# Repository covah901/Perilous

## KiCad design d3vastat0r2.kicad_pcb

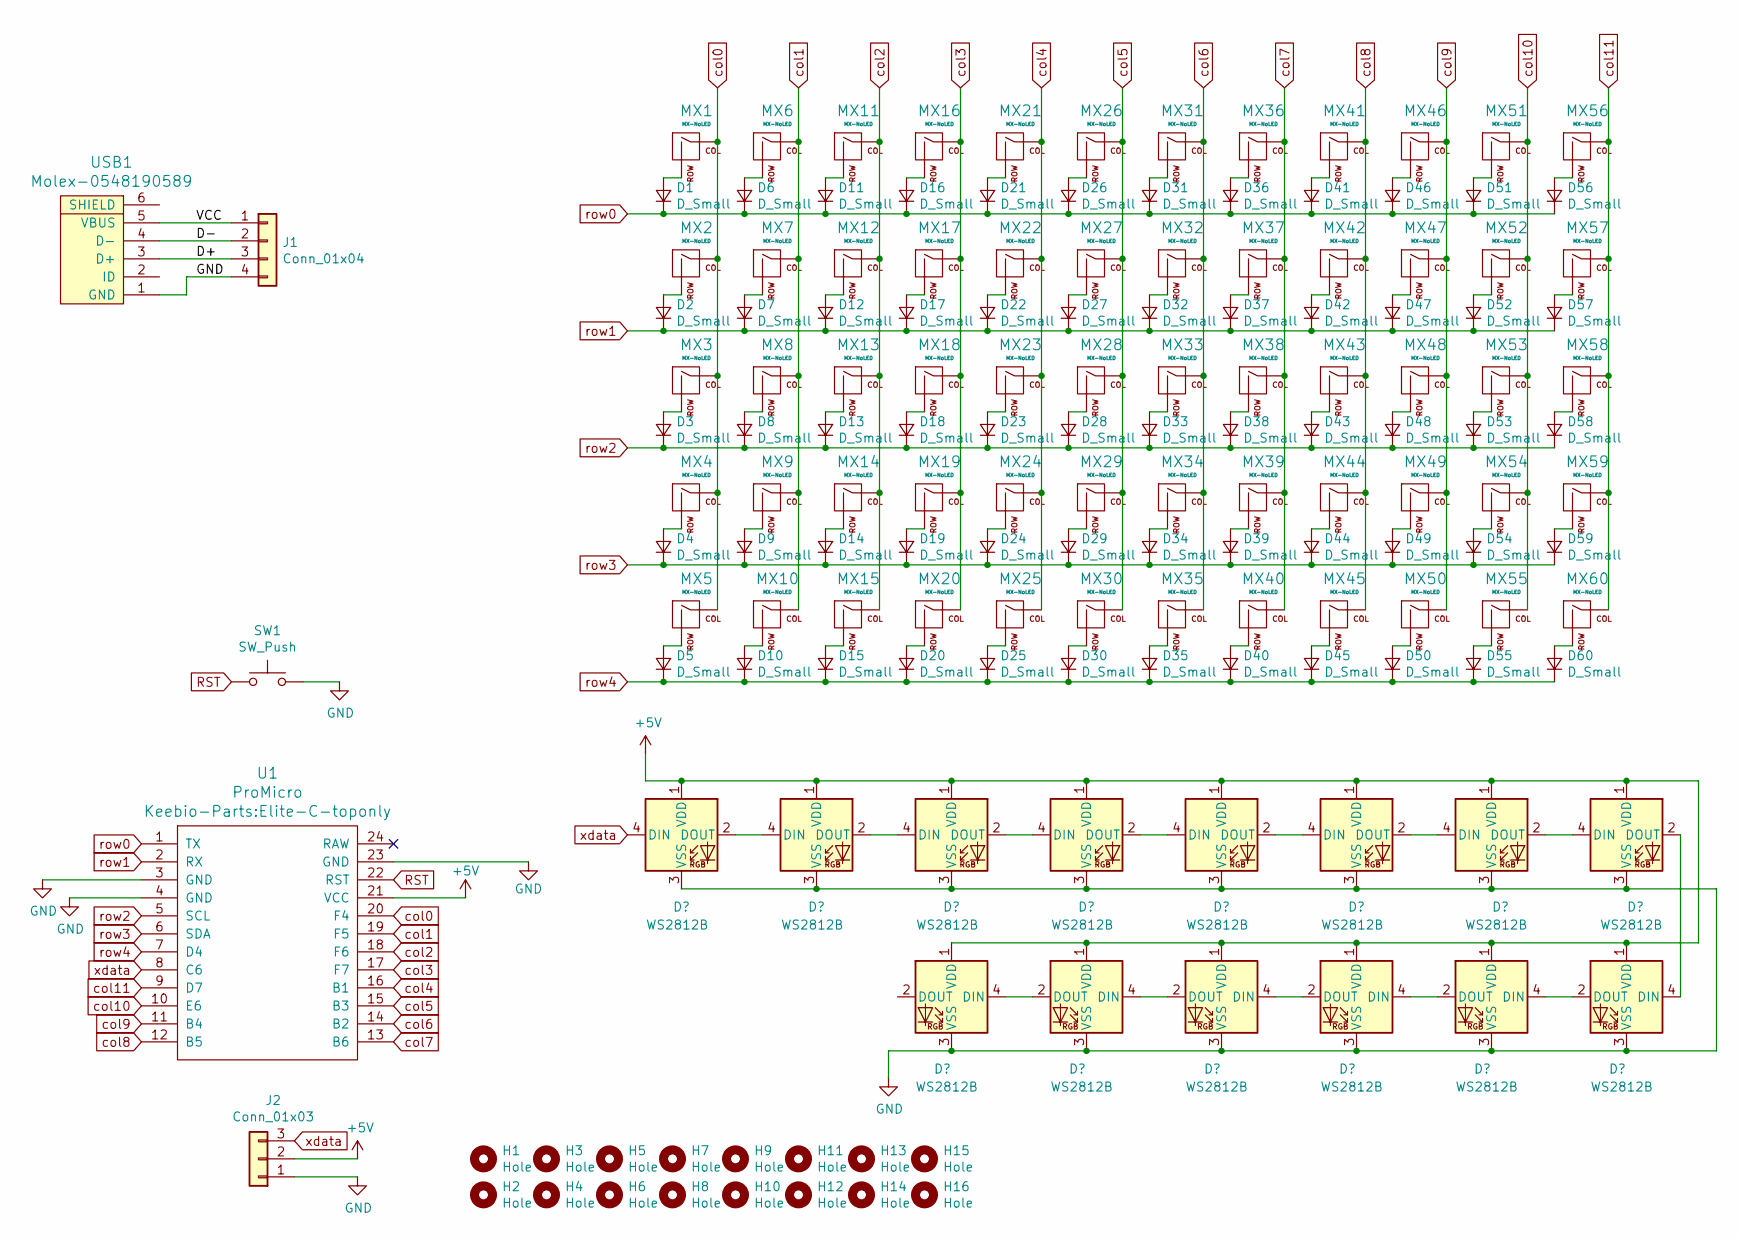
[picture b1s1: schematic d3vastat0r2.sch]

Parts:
D1, D2, D3, D4, D5, D6, D7, D8, D9, D10, D11, D12, D13, D14, D15, D16, D17, D18, D19, D20, D21, D22, D23, D24, D25, D26, D27, D28, D29, D30, D31, D32, D33, D34, D35, D36, D37, D38, D39, D40, D41, D42, D43, D44, D45, D46, D47, D48, D49, D50, D51, D52, D53, D54, D55, D56, D57, D58, D59, D60: D_Small; Diode-dual
H1, H2, H3, H4, H5, H6, H7, H8, H9, H10, H11, H12, H13, H14, H15, H16: Hole; MountingHole_2.2mm_M2_DIN965_Pad
J1: Conn_01x04; SolderWirePad_1x04_P3.81mm_Drill1mm
J2: Conn_01x03; SolderWirePad_1x03_P3.175mm_Drill1mm
MX1, MX5, MX6, MX7, MX8, MX9, MX10, MX11, MX12, MX13, MX14, MX15, MX16, MX17, MX18, MX19, MX21, MX22, MX23, MX24, MX26, MX27, MX28, MX29, MX31, MX32, MX33, MX34, MX36, MX37, MX38, MX39, MX41, MX42, MX43, MX44, MX45, MX46, MX47, MX48, MX49, MX50, MX51, MX52, MX53, MX54, MX55, MX56, MX60: MX-NoLED; MXOnly-1U-NoLED
MX2, MX20, MX25, MX40, MX57: MX-NoLED; MXOnly-1.5U-NoLED
MX3: MX-NoLED; MXOnly-1.75U-NoLED
MX4, MX58, MX59: MX-NoLED; MXOnly-2.25U-NoLED
MX30, MX35: MX-NoLED; MXOnly-2U-NoLED
SW1: SW_Push; SKQG-1155865
U1: ProMicro; Elite-C-toponly
USB1: Molex-0548190589; USB-Mini-B_ LCSC-C46398

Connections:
+5V: J2.2, U1.21 (VCC)
/D+: J1.3, USB1.3 (D+)
/D-: J1.2, USB1.4 (D-)
/VCC: J1.1, USB1.5 (VBUS)
GND: J1.4, J2.1, SW1.2, U1.3 (GND), U1.4 (GND), U1.23 (GND), USB1.1 (GND)
unnamed: D1.2 (A), MX1.2 (ROW)
unnamed: D2.2 (A), MX2.2 (ROW)
unnamed: D3.2 (A), MX3.2 (ROW)
unnamed: D4.2 (A), MX4.2 (ROW)
unnamed: D5.2 (A), MX5.2 (ROW)
unnamed: D6.2 (A), MX6.2 (ROW)
unnamed: D7.2 (A), MX7.2 (ROW)
unnamed: D8.2 (A), MX8.2 (ROW)
unnamed: D9.2 (A), MX9.2 (ROW)
unnamed: D10.2 (A), MX10.2 (ROW)
unnamed: D11.2 (A), MX11.2 (ROW)
unnamed: D12.2 (A), MX12.2 (ROW)
unnamed: D13.2 (A), MX13.2 (ROW)
unnamed: D14.2 (A), MX14.2 (ROW)
unnamed: D15.2 (A), MX15.2 (ROW)
unnamed: D16.2 (A), MX16.2 (ROW)
unnamed: D17.2 (A), MX17.2 (ROW)
unnamed: D18.2 (A), MX18.2 (ROW)
unnamed: D19.2 (A), MX19.2 (ROW)
unnamed: D20.2 (A), MX20.2 (ROW)
unnamed: D21.2 (A), MX21.2 (ROW)
unnamed: D22.2 (A), MX22.2 (ROW)
unnamed: D23.2 (A), MX23.2 (ROW)
unnamed: D24.2 (A), MX24.2 (ROW)
unnamed: D25.2 (A), MX25.2 (ROW)
unnamed: D26.2 (A), MX26.2 (ROW)
unnamed: D27.2 (A), MX27.2 (ROW)
unnamed: D28.2 (A), MX28.2 (ROW)
unnamed: D29.2 (A), MX29.2 (ROW)
unnamed: D30.2 (A), MX30.2 (ROW)
unnamed: D31.2 (A), MX31.2 (ROW)
unnamed: D32.2 (A), MX32.2 (ROW)
unnamed: D33.2 (A), MX33.2 (ROW)
unnamed: D34.2 (A), MX34.2 (ROW)
unnamed: D35.2 (A), MX35.2 (ROW)
unnamed: D36.2 (A), MX36.2 (ROW)
unnamed: D37.2 (A), MX37.2 (ROW)
unnamed: D38.2 (A), MX38.2 (ROW)
unnamed: D39.2 (A), MX39.2 (ROW)
unnamed: D40.2 (A), MX40.2 (ROW)
unnamed: D41.2 (A), MX41.2 (ROW)
unnamed: D42.2 (A), MX42.2 (ROW)
unnamed: D43.2 (A), MX43.2 (ROW)
unnamed: D44.2 (A), MX44.2 (ROW)
unnamed: D45.2 (A), MX45.2 (ROW)
unnamed: D46.2 (A), MX46.2 (ROW)
unnamed: D47.2 (A), MX47.2 (ROW)
unnamed: D48.2 (A), MX48.2 (ROW)
unnamed: D49.2 (A), MX49.2 (ROW)
unnamed: D50.2 (A), MX50.2 (ROW)
unnamed: D51.2 (A), MX51.2 (ROW)
unnamed: D52.2 (A), MX52.2 (ROW)
unnamed: D53.2 (A), MX53.2 (ROW)
unnamed: D54.2 (A), MX54.2 (ROW)
unnamed: D55.2 (A), MX55.2 (ROW)
unnamed: D56.2 (A), MX56.2 (ROW)
unnamed: D57.2 (A), MX57.2 (ROW)
unnamed: D58.2 (A), MX58.2 (ROW)
unnamed: D59.2 (A), MX59.2 (ROW)
unnamed: D60.2 (A), MX60.2 (ROW)
RST: SW1.1, U1.22 (RST)
col0: MX1.1 (COL), MX2.1 (COL), MX3.1 (COL), MX4.1 (COL), MX5.1 (COL), U1.20 (F4)
col1: MX6.1 (COL), MX7.1 (COL), MX8.1 (COL), MX9.1 (COL), MX10.1 (COL), U1.19 (F5)
col2: MX11.1 (COL), MX12.1 (COL), MX13.1 (COL), MX14.1 (COL), MX15.1 (COL), U1.18 (F6)
col3: MX16.1 (COL), MX17.1 (COL), MX18.1 (COL), MX19.1 (COL), MX20.1 (COL), U1.17 (F7)
col4: MX21.1 (COL), MX22.1 (COL), MX23.1 (COL), MX24.1 (COL), MX25.1 (COL), U1.16 (B1)
col5: MX26.1 (COL), MX27.1 (COL), MX28.1 (COL), MX29.1 (COL), MX30.1 (COL), U1.15 (B3)
col6: MX31.1 (COL), MX32.1 (COL), MX33.1 (COL), MX34.1 (COL), MX35.1 (COL), U1.14 (B2)
col7: MX36.1 (COL), MX37.1 (COL), MX38.1 (COL), MX39.1 (COL), MX40.1 (COL), U1.13 (B6)
col8: MX41.1 (COL), MX42.1 (COL), MX43.1 (COL), MX44.1 (COL), MX45.1 (COL), U1.12 (B5)
col9: MX46.1 (COL), MX47.1 (COL), MX48.1 (COL), MX49.1 (COL), MX50.1 (COL), U1.11 (B4)
col10: MX51.1 (COL), MX52.1 (COL), MX53.1 (COL), MX54.1 (COL), MX55.1 (COL), U1.10 (E6)
col11: MX56.1 (COL), MX57.1 (COL), MX58.1 (COL), MX59.1 (COL), MX60.1 (COL), U1.9 (D7)
row0: D1.1 (K), D6.1 (K), D11.1 (K), D16.1 (K), D21.1 (K), D26.1 (K), D31.1 (K), D36.1 (K), D41.1 (K), D46.1 (K), D51.1 (K), D56.1 (K), U1.1 (TX)
row1: D2.1 (K), D7.1 (K), D12.1 (K), D17.1 (K), D22.1 (K), D27.1 (K), D32.1 (K), D37.1 (K), D42.1 (K), D47.1 (K), D52.1 (K), D57.1 (K), U1.2 (RX)
row2: D3.1 (K), D8.1 (K), D13.1 (K), D18.1 (K), D23.1 (K), D28.1 (K), D33.1 (K), D38.1 (K), D43.1 (K), D48.1 (K), D53.1 (K), D58.1 (K), U1.5 (SCL)
row3: D4.1 (K), D9.1 (K), D14.1 (K), D19.1 (K), D24.1 (K), D29.1 (K), D34.1 (K), D39.1 (K), D44.1 (K), D49.1 (K), D54.1 (K), D59.1 (K), U1.6 (SDA)
row4: D5.1 (K), D10.1 (K), D15.1 (K), D20.1 (K), D25.1 (K), D30.1 (K), D35.1 (K), D40.1 (K), D45.1 (K), D50.1 (K), D55.1 (K), D60.1 (K), U1.7 (D4)
xdata: J2.3, U1.8 (C6)

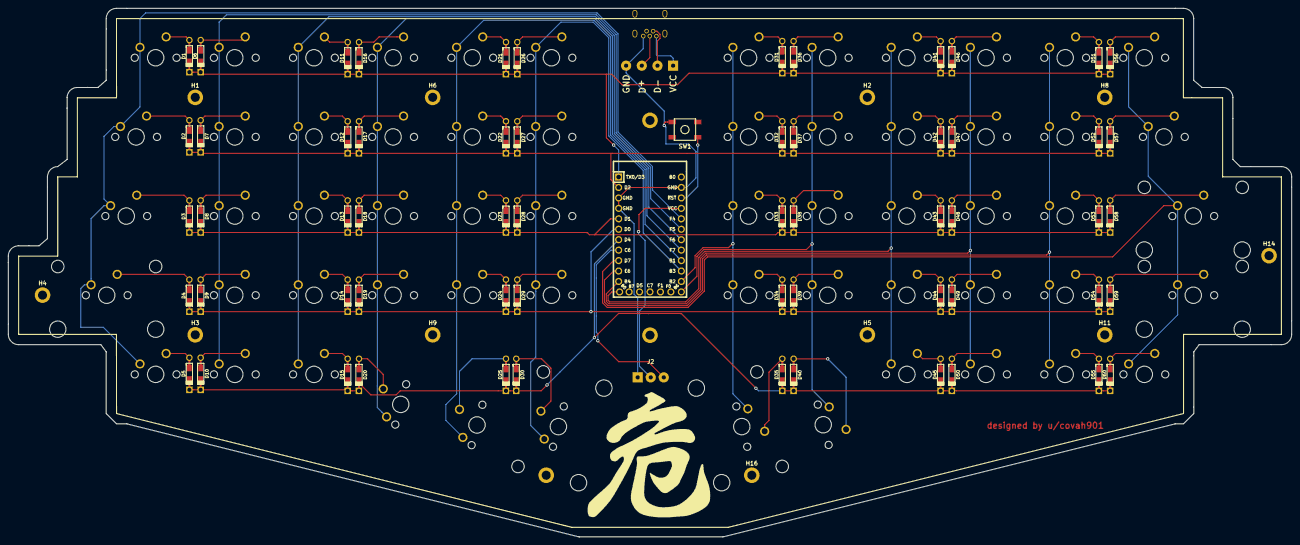
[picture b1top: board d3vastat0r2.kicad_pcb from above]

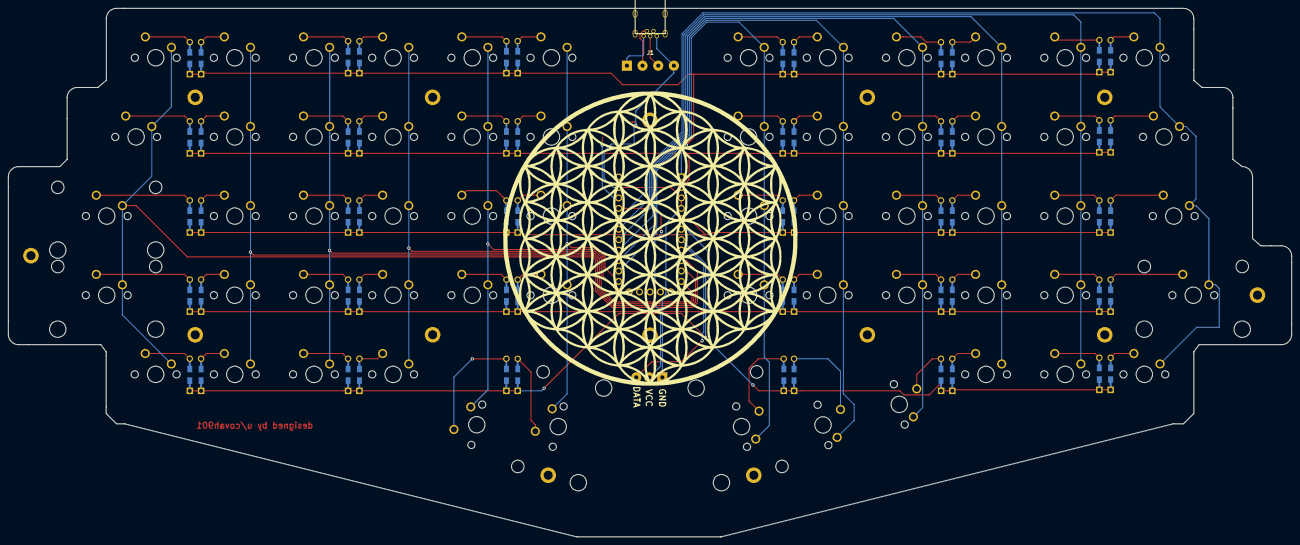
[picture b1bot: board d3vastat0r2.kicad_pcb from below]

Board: 2 copper layers, 312.1 x 128.6 mm, 139 parts (2 on the bottom side), 84 nets.
